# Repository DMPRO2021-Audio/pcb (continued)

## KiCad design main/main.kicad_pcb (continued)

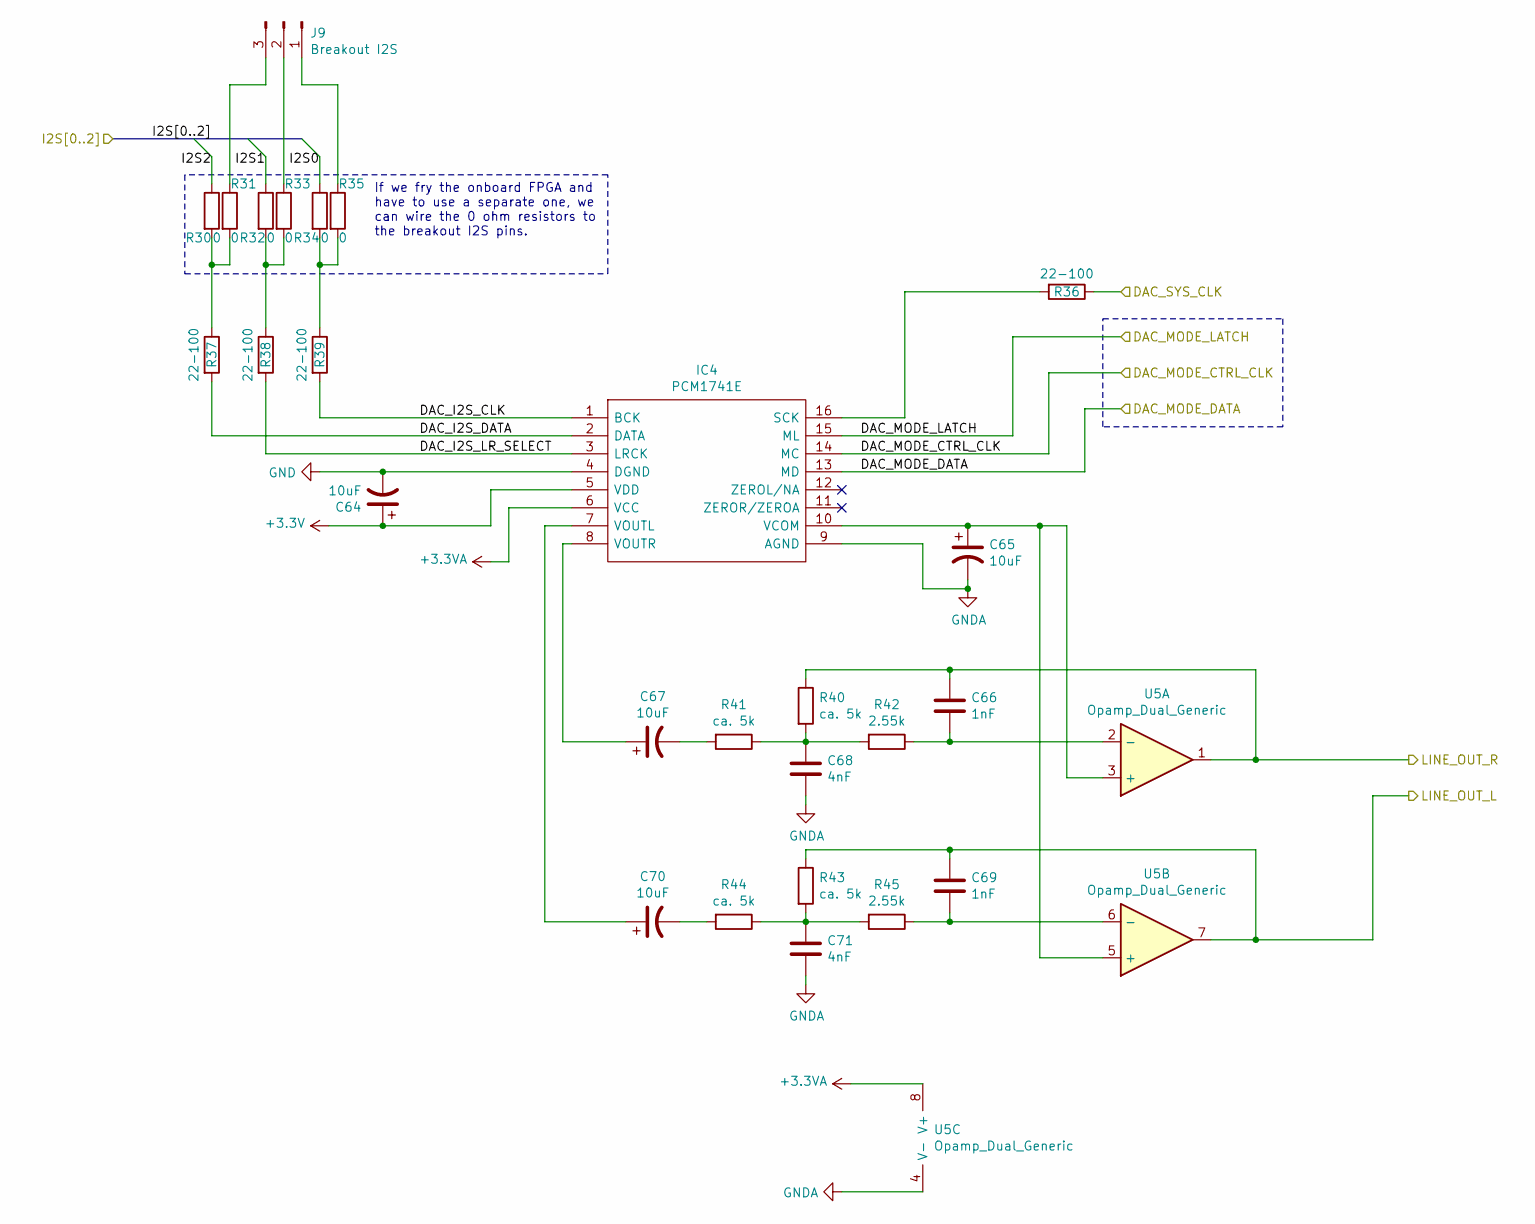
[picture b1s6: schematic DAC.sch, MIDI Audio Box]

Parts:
C64, C65, C67, C70: 10uF; CP_EIA-3528-12_Kemet-T_Pad1.50x2.35mm_HandSolder
C66, C69: 1nF; C_0805_2012Metric_Pad1.18x1.45mm_HandSolder
C68, C71: 4nF; C_0805_2012Metric_Pad1.18x1.45mm_HandSolder
IC4: PCM1741E; SOP63P600X175-16N; Manufacturer_Part_Number PCM1741E; Mouser Part Number 595-PCM1741E
J9: Breakout I2S; PinHeader_1x03_P2.54mm_Vertical
R30, R32, R34: 0; SolderJumper-2_P1.3mm_Bridged2Bar_RoundedPad1.0x1.5mm
R31, R33, R35: 0; SolderJumper-2_P1.3mm_Open_RoundedPad1.0x1.5mm
R36, R37, R38, R39: 22-100; R_0805_2012Metric_Pad1.20x1.40mm_HandSolder
R40, R41, R43, R44: ca. 5k; R_0805_2012Metric_Pad1.20x1.40mm_HandSolder
R42, R45: 2.55k; R_0805_2012Metric_Pad1.20x1.40mm_HandSolder
U5: Opamp_Dual_Generic; SOIC-8_5.23x5.23mm_P1.27mm; Manufacturer_Part_Number OPA2353UA

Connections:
+3.3VA: IC4.6 (VCC), U5.8 (V+); also elsewhere on the board
+3V3: C64.1, IC4.5 (VDD); also elsewhere on the board
/DAC/DAC_I2S_CLK: IC4.1 (BCK), R39.2
/DAC/DAC_I2S_DATA: IC4.2 (DATA), R37.2
/DAC/DAC_I2S_LR_SELECT: IC4.3 (LRCK), R38.2
/DAC/DAC_MODE_CTRL_CLK: IC4.14 (MC); also elsewhere on the board
/DAC/DAC_MODE_DATA: IC4.13 (MD); also elsewhere on the board
/DAC/DAC_MODE_LATCH: IC4.15 (ML); also elsewhere on the board
/DAC/DAC_SYS_CLK: R36.1; also elsewhere on the board
/DAC/I2S0: R34.1; also elsewhere on the board
/DAC/I2S1: R32.1; also elsewhere on the board
/DAC/I2S2: R30.1; also elsewhere on the board
/DAC/LINE_OUT_L: C69.1, R43.1, U5.7; also elsewhere on the board
/DAC/LINE_OUT_R: C66.1, R40.1, U5.1; also elsewhere on the board
GND: C64.2, C65.2, C68.2, C71.2, IC4.4 (DGND), IC4.9 (AGND), U5.4 (V-); also elsewhere on the board
unnamed: C65.1, IC4.10 (VCOM), U5.3 (+), U5.5 (+)
unnamed: C66.2, R42.1, U5.2 (-)
unnamed: C67.1, IC4.8 (VOUTR)
unnamed: C67.2, R41.2
unnamed: C68.1, R40.2, R41.1, R42.2
unnamed: C69.2, R45.1, U5.6 (-)
unnamed: C70.1, IC4.7 (VOUTL)
unnamed: C70.2, R44.2
unnamed: C71.1, R43.2, R44.1, R45.2
unnamed: IC4.16 (SCK), R36.2
unnamed: J9.1, R35.1
unnamed: J9.2, R33.1
unnamed: J9.3, R31.1
unnamed: R30.2, R31.2, R37.1
unnamed: R32.2, R33.2, R38.1
unnamed: R34.2, R35.2, R39.1

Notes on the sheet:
If we fry the onboard FPGA and have to use a separate one, we can wire the 0 ohm resistors to the breakout I2S pins.

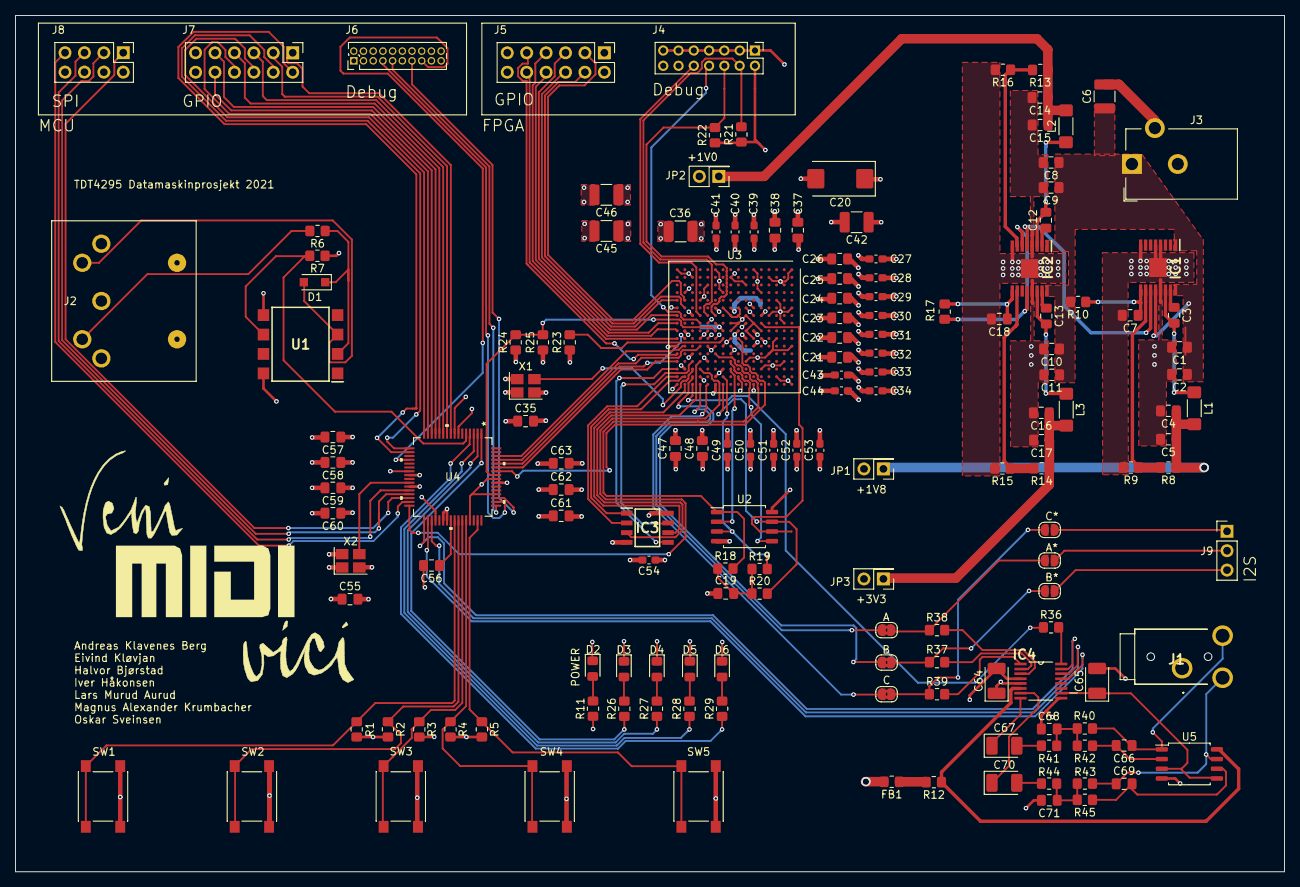
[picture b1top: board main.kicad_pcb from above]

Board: 4 copper layers, 166.0 x 112.0 mm, 156 parts (0 on the bottom side), 123 nets.

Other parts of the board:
logo: G***; logo
svg2mod: G***; logo

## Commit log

2021-09-06 Init
2021-09-06 Add MIDI-IN connector
2021-09-06 Implement MIDI input circuit.
2021-09-07 Add debug interface
2021-09-07 Moved some stuff around
2021-09-08 Add EFM32GG component library
2021-09-08 Place separate parts in hierarchical sheets, connect in main schematic
2021-09-08 Some cleanup
2021-09-09 Add PCM1780DBQ (DAC) lib
2021-09-09 Add PCM1780DBQ footprint
2021-09-09 Add DAC to bill of materials
2021-09-09 Add hierarichal sheet for FPGA
    Not done yet
2021-09-13 Add rotary encoders
2021-09-13 Setup DAC.
2021-09-13 Used wrong MIDI connector
2021-09-13 Add DIN to README
2021-09-13 Add DAC footprint
2021-09-14 Move EFM32GG debug port inside MCU sheet
2021-09-14 Simplify the top sheet, put bus connection inside the sheets
2021-09-15 Setup FPGA power connections, connect FPGA flash
2021-09-15 Finish (?) setting up FPGA as in the slides
2021-09-15 Add FPGA oscillator, cleanup
2021-09-16 Add the MCU we will be using, try setting up power connections
2021-09-16 Some small changes
2021-09-16 Add basic amplifier circuit
    Haven't yet added values for capacitors or resistors.
    Calculations seem quite straight forward though.
2021-09-17 Update BoM
2021-09-17 Remove old DAC files. Connect amplifier to audio out
2021-09-17 Add some component values to AMP
2021-09-20 Set up switching regulator circuits.
    We only use half of the switching regulator that generates the 1V0
    voltage. I'm not sure if the half not being used is connected correctly.
2021-09-20 Remove old EFM32GG lib
2021-09-20 Continue wiring of the MCU
2021-09-21 Be consistent with capacitor values (always use F)
2021-09-21 FPGA connections, DAC linear regulator removed, DAC I2S breakout
    Connected the SPI, I2S and GPIO to some (mostly) arbitrary pins. Notably
    the SPI clock has to be connected to a clock pin on the FPGA.
    The linear regulator is (hopefully) not needed for the DAC as we already
    have a separate analog +3.3V created by the switching regulators.
    The I2S wires to the DAC are now connected to the FPGA as well as
    breakout pins over 0 ohm resistors, in case we need to connect to an
2021-09-23 Some tweaks
2021-09-23 Add FPGA RAM chip
2021-09-23 Final cleanup before sending in for rebiew
2021-09-24 Fix up after review
    Done:
    - Add bulk decoupling capacitor to switch regulator cirucit
    - Disconnect DONE from PROGRAM_B in FPGA (mistake)
    - The decoupling capacitors used for the FPGA were for the 15T, not the
    100T. It was also setup for two I/O banks, we only use one. Disconnect
    I/O bank 15.
2021-09-24 Fix up after review 2
    Don't route DAC_ZERO_{L,R} through FPGA into SHUTDOWN on the amp, it is
    not really necessary and just adds routing complexity.
2021-09-24 Fix up after review 3
    Add +3.3V and GND to MCU and FPGA GPIO.
    Add a lot of footprints.
2021-09-27 DAC: Remove amplifier, replace with low pass as per datasheet
    Also: a lot of footprint association
2021-09-27 Start PCB layout
2021-09-27 Continue PCB layout
2021-09-28 Some more routing
2021-09-28 PCB getting close to being fully connected
    Still missing the power circuit, will look at it tomorrow.
2021-09-29 Almost finished with PCB layout
    - Fixed FPGA power layout. The 1V0, 1V8 and 3V3 pins have to be
    connected to vias which in turn connect to fat lanes
    - Added logo and names
    - Started power circuit, this needs some work
2021-09-30 Finished (?) board
2021-09-30 Fixes after review
    - +1V0 and +1V8 power zones on the backside of the FPGA
    - Vias directly next to decoupling capacitors
2021-09-30 Fix MCU silk
2021-11-18 Link to correct BOM
2021-11-18 Add missing junction
2021-11-18 Add missing resistor to power supply
2021-11-23 Create LICENSE
